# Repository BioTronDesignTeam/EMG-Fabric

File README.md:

June 28: added the connections in PCB/KiCAD/STM3_ADS1299 folder

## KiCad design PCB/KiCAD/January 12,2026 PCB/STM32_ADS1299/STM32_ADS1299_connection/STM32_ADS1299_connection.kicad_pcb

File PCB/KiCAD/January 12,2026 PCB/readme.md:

This file contains the pcb that connects the emg sensors, esp32 and lipo battery. This version is from January 12,2026 and the first PCB print of this projectt.

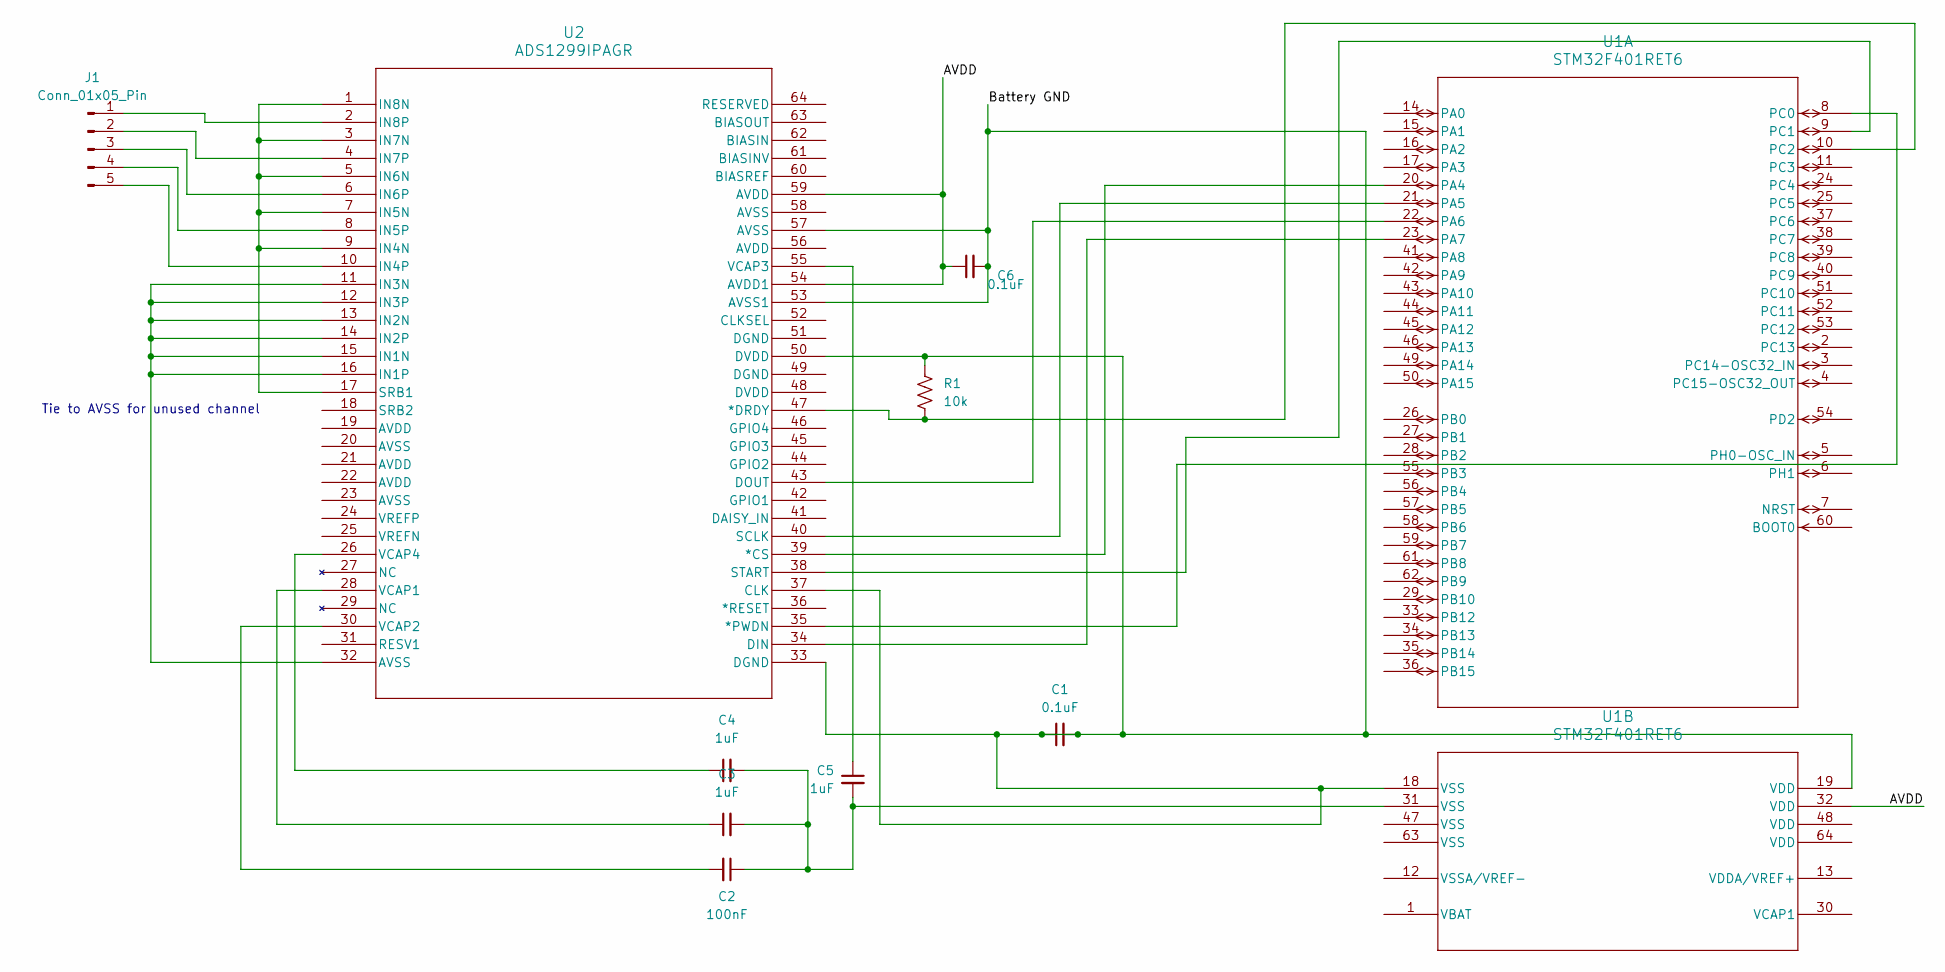
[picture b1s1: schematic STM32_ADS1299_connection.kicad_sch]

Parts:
C1, C6: 0.1uF; C_01005_0402Metric
C2: 100nF; C_01005_0402Metric
C3, C4, C5: 1uF; C_01005_0402Metric
J1: Conn_01x05_Pin; PinHeader_1x05_P2.54mm_Horizontal
R1: 10k; R_01005_0402Metric
U1: STM32F401RET6; LQFP64-10x10mm
U2: ADS1299IPAGR; PAG64_TEX-M

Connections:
/AVDD: C6.1, U1.32 (VDD), U2.54 (AVDD1), U2.59 (AVDD)
/Battery GND: C1.1, C1.2, C6.2, R1.1, U1.18 (VSS), U1.19 (VDD), U2.33 (DGND), U2.37 (CLK), U2.50 (DVDD), U2.53 (AVSS1), U2.57 (AVSS)
unnamed: C2.1, C3.2, C4.2, C5.2, U1.31 (VSS)
unnamed: J1.1, U2.2 (IN8P)
unnamed: J1.2, U2.4 (IN7P)
unnamed: J1.3, U2.6 (IN6P)
unnamed: J1.4, U2.8 (IN5P)
unnamed: J1.5, U2.10 (IN4P)
unnamed: U1.20 (PA4), U2.39 (*CS)
unnamed: U1.21 (PA5), U2.40 (SCLK)
unnamed: U1.22 (PA6), U2.43 (DOUT)
unnamed: U1.23 (PA7), U2.34 (DIN)
unnamed: U1.8 (PC0), U2.35 (*PWDN)
unnamed: U1.9 (PC1), U2.38 (START)
unnamed: R1.2, U1.10 (PC2), U2.47 (*DRDY)
unnamed: U2.11 (IN3N), U2.12 (IN3P), U2.13 (IN2N), U2.14 (IN2P), U2.15 (IN1N), U2.16 (IN1P), U2.32 (AVSS)
unnamed: U2.1 (IN8N), U2.3 (IN7N), U2.5 (IN6N), U2.7 (IN5N), U2.9 (IN4N), U2.17 (SRB1)
unnamed: C3.1, U2.28 (VCAP1)
unnamed: C2.2, U2.30 (VCAP2)
unnamed: C5.1, U2.55 (VCAP3)
unnamed: C4.1, U2.26 (VCAP4)

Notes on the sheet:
Tie to AVSS for unused channel

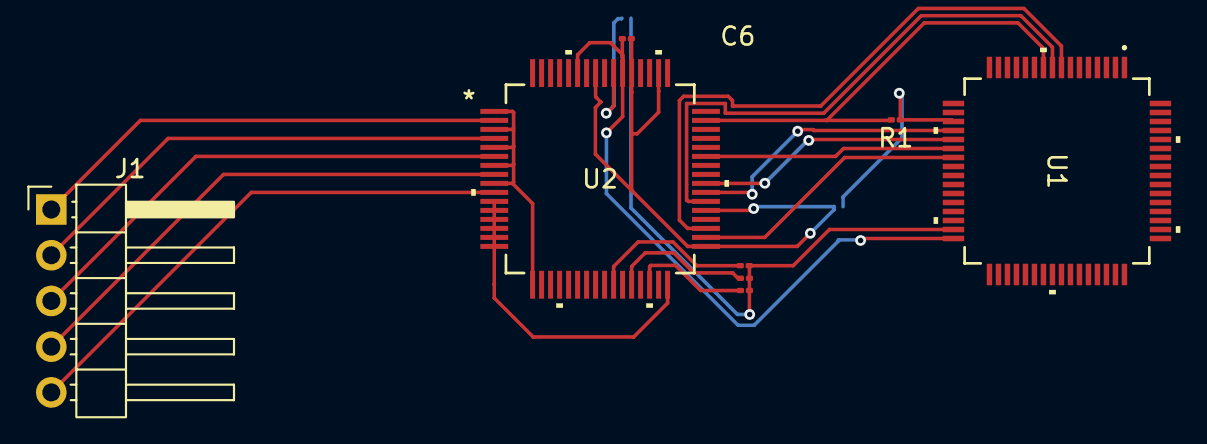
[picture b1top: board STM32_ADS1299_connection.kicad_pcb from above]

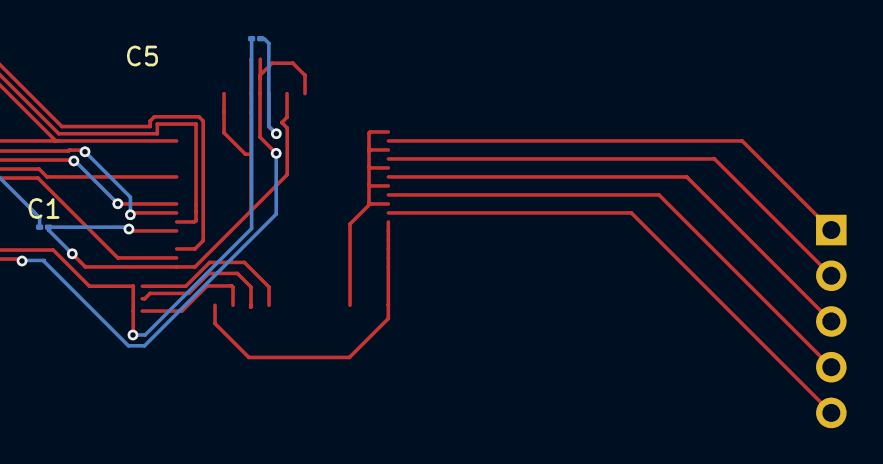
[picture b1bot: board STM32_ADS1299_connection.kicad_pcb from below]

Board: 2 copper layers, 10 parts (2 on the bottom side), 21 nets.

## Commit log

2024-11-06 Create test
2025-03-31 add glove component sldprts
2025-05-27 added stepper motor and assembly files
2025-06-03 fixed spool gear
2025-06-03 test
2025-06-09 motor gear
2025-06-09 Created axle with integrated gear and fixed both other gears (teeth were slightly off center)
2025-06-10 added bearing, stand, assembly
2025-06-10 new base
2025-06-12 completed Palmar assembly
2025-07-22 reduced length to 60mm, reduced height
2025-07-24 Base with simple motor mount
2025-07-25 2nd version, added STL files
2026-01-12 Rename 5972K501_Ball Bearing.SLDPRT to 5972K501_Ball Bearing.SLDPRT
2026-01-12 Rename SensorCaseLidRedesign.SLDPRT to SensorCaseLidRedesign.SLDPRT
2026-01-12 Rename SensorCaseRedesign.SLDPRT to SensorCaseRedesign.SLDPRT
2026-01-13 Rename SensorCaseRedesignAssembly.SLDASM to SensorCaseRedesignAssembly.SLDASM
2026-01-13 Rename bent_ext.SLDPRT to bent_ext.SLDPRT
2026-01-13 Rename Mechanical/Exoskeleton/CombinedBase.SLDPRT to Mechanical Prototypes/Palmar Exoskeleton/Version 1 (S25)/CombinedBase.SLDPRT
2026-01-13 Rename Mechanical/Exoskeleton/Glove string spool.SLDPRT to Mechanical Prototypes/Palmar Exoskeleton/Version 1 (S25)/Glove string spool.SLDPRT
2026-01-13 Rename Mechanical/Exoskeleton/New Motor Gear.SLDPRT to Mechanical Prototypes/Palmar Exoskeleton/Version 1 (S25)/New Motor Gear.SLDPRT
2026-01-13 Rename Mechanical/Exoskeleton/New Spool Gear.SLDPRT to Mechanical Prototypes/Palmar Exoskeleton/Version 1 (S25)/New Spool Gear.SLDPRT
2026-01-13 Rename Mechanical/Exoskeleton/NewBaseWithMount.SLDPRT to Mechanical Prototypes/Palmar Exoskeleton/Version 1 (S25)/NewBaseWithMount.SLDPRT
2026-01-13 Rename Mechanical/Exoskeleton/Palmar_Exoskeleton.SLDASM to Mechanical Prototypes/Palmar Exoskeleton/Version 1 (S25)/Palmar_Exoskeleton.SLDASM
2026-01-13 Rename Mechanical/Exoskeleton/Print2.makerbot to Mechanical Prototypes/Palmar Exoskeleton/Version 1 (S25)/Print2.makerbot
2026-01-13 Rename Mechanical/Exoskeleton/Project.print to Mechanical Prototypes/Palmar Exoskeleton/Version 1 (S25)/Project.print
2026-01-13 Rename Mechanical/Exoskeleton/Project2.print to Mechanical Prototypes/Palmar Exoskeleton/Version 1 (S25)/Project2.print
2026-01-13 Rename Mechanical/Exoskeleton/Stepper motor 28BYJ-48 5V.SLDPRT to Mechanical Prototypes/Palmar Exoskeleton/Version 1 (S25)/Stepper motor 28BYJ-48 5V.SLDPRT
2026-01-13 Rename Mechanical/Exoskeleton/STL Files/BaseWithMount.STL to Mechanical Prototypes/Palmar Exoskeleton/Version 1 (S25)/STL Files/BaseWithMount.STL
2026-01-13 Rename Mechanical/Exoskeleton/STL Files/Glove string spool.STL to Mechanical Prototypes/Palmar Exoskeleton/Version 1 (S25)/STL Files/Glove string spool.STL
2026-01-13 Rename Mechanical/Exoskeleton/STL Files/New Motor Gear.STL to Mechanical Prototypes/Palmar Exoskeleton/Version 1 (S25)/STL Files/New Motor Gear.STL
2026-01-13 Rename Mechanical/Exoskeleton/STL Files/New Spool Gear.STL to Mechanical Prototypes/Palmar Exoskeleton/Version 1 (S25)/STL Files/New Spool Gear.STL
2026-01-13 Rename Mechanical/Exoskeleton/STL Files/NewBaseWithMount.STL to Mechanical Prototypes/Palmar Exoskeleton/Version 1 (S25)/STL Files/NewBaseWithMount.STL
2026-01-13 Rename Mechanical Prototypes/Exoskeleton/5972K501_Ball Bearing.SLDPRT to Mechanical Prototypes/Palmar Exoskeleton/Version 1 (S25)/5972K501_Ball Bearing.SLDPRT
2026-01-13 Create Group 2 (S25)
2026-01-13 Create KiCAD
2026-01-13 Create Altium
2026-01-13 Add files via upload
    https://cad.onshape.com/documents/414a09d978d5760cfb573294/w/9651158a6d41aada65b1d957/e/554b3252b191393066c26a78?renderMode=0&uiState=696595921d49c1d03b418732
2026-01-13 Add readme for January 12, 2026 PCB design
2026-01-13 added cads
2026-01-13 imported kicad to altium, TODO: footprint check
2026-01-13 Add imported Altium PCB, fixed file name
2026-01-15 Added software files
2026-01-15 Added requirements.txt
2026-01-15 Add ML content
2026-01-16 Add readme file for Jax's Cool Designs
2026-01-16 Add initial readme for Single_Proto_2
2026-01-16 Add initial content to readme in 4_Clips
2026-01-16 Create Servo_Parts
2026-01-16 Add initial content to Servo_Parts readme
2026-01-16 Add initial readme for Gearbox design
2026-01-16 Add new file for pictures and videos
2026-06-22 started kicad project
2026-06-24 KiCad sheet set up and added ADS1299IPAGR in libraries folder for external footprints and symbols.
2026-06-26 Added STM32F401RET6 footprint and symbol to project and MCU sheet
2026-06-28 Added STM32 and ADS1299 Schematic connection and quick trace connection
2026-06-28 Commit to submodule reference on Jun_PCB
2026-06-28 Reorganizing folders
